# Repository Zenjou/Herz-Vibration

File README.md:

# Herz Vibration
Project for Electronic Equipment Design Course ( ELO301 Federico Santa María Technical University)

Group 6 
 - Victor Muñoz Salinas
 - Josefa Gomez
 - Diego Muñoz
 - Maximiliano Lara

# Description:
This project focuses on designing a PCB for real-time seismocardiograms utilizing geophones. Geophones efficiently capture vibrations produced by cardiac activity (Seismocardiography) . The custom-designed PCB seamlessly integrates with existing software, enabling efficient signal processing and in-depth analysis. Eagle PCB schematics, manufacturing files (including Gerber files and drill files), and a comprehensive Bill of Materials (BOM) are provided for straightforward replication.

# Features:
Custom-designed PCB optimized for seamless integration with geophones.

Eagle PCB schematics for a thorough understanding and easy modification.

Inclusion of all essential manufacturing files, including Gerber files and drill files, for PCB fabrication.

Utilizes the STM32 NUCLEO-L452 development board for enhanced functionality.

# Technologies Used:
Eagle PCB for schematic design.

Geophonic sensors for vibration capture (3 Geophones for each axis).

STM32 NUCLEO-L452 development board.

**SerialPlot by Hasan Yavuz Özderya for graphical visualization.**

ADS131M03 3-channel, 24-bit, 64 kSPS simultaneous sampling delta-sigma ADC.

# Files:
Eagle PCB Schematics

Manufacturing Files (Gerber, Drill Files, etc.)

BOM File

Videos

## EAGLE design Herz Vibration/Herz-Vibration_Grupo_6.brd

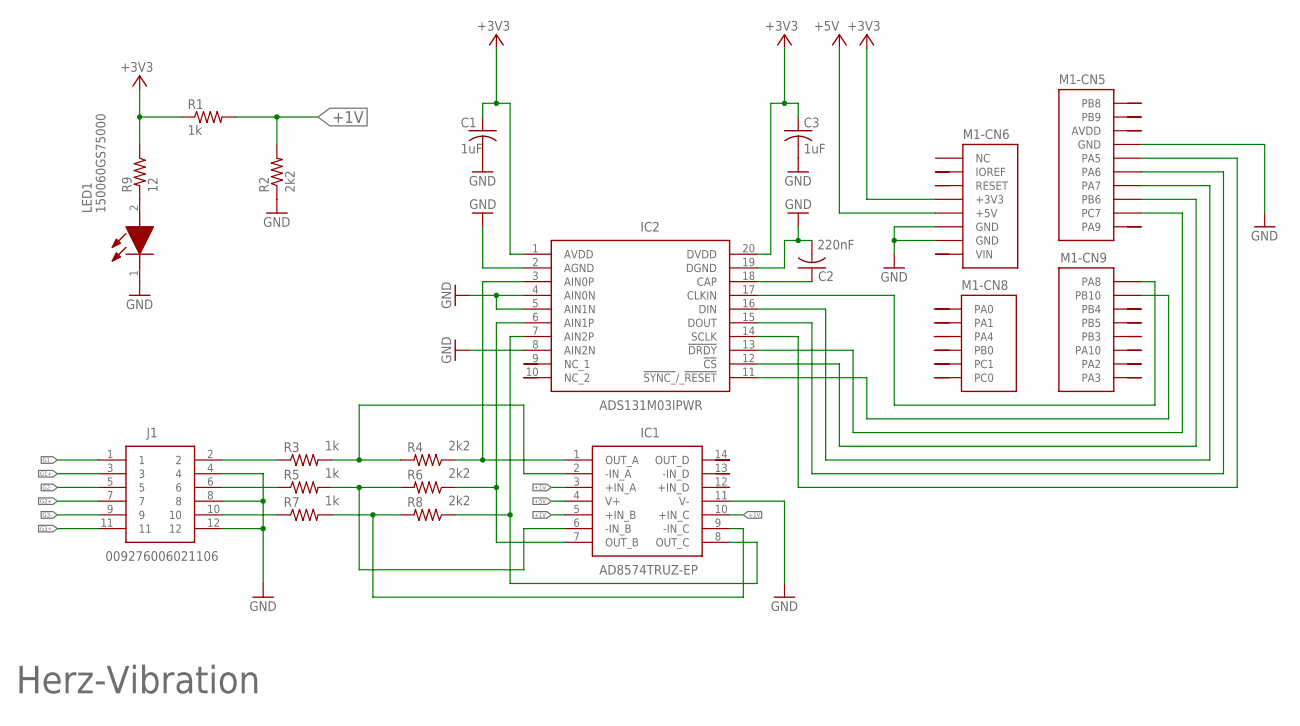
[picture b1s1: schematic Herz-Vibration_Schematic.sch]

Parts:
C1, C3: 1uF; C0805; PARTNO C1206C105K3RAC7215
C2: 220nF; C0805; PARTNO 885382207008
IC1: AD8574TRUZ-EP; SOP65P640X120-14N
IC2: ADS131M03IPWR; SOP65P640X120-20N
J1: 009276006021106
LED1: 150060GS75000; LEDC1608X80N
M1: NUCLEO-L452RE; NUCLEO-64
R1, R3, R5, R7: 1k; R0805; PARTNO TNPW04021K15BYEP
R2, R4, R6, R8: 2k2; R0805; PARTNO RP0603BRD072K2L
R9: 12; R0805; PARTNO RT0603DRE0712RL

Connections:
+1V: IC1.3 (+IN_A), IC1.5 (+IN_B), IC1.10 (+IN_C), R1.2, R2.2
+3V3: C1.1, C3.1, IC2.1 (AVDD), IC2.20 (DVDD), M1.CN6-4 (+3V3), M1.CN7-16 (+3V3), R1.1, R9.1
+5V: IC1.4 (V+), M1.CN6-5 (+5V), M1.CN7-18 (+5V)
AGND: M1.CN10-32 (AGND)
AVDD: M1.CN10-7 (AVDD)
G1+: J1.3
G1-: J1.1
G2+: J1.7
G2-: J1.5
G3+: J1.11
G3-: J1.9
GND: C1.2, C2.2, C3.2, IC1.11 (V-), IC2.2 (AGND), IC2.4 (AIN0N), IC2.5 (AIN1N), IC2.8 (AIN2N), IC2.19 (DGND), J1.4, J1.8, J1.12, LED1.1 (K), M1.CN5-7 (GND), M1.CN6-6 (GND), M1.CN6-7 (GND), M1.CN7-8 (GND), M1.CN7-19 (GND), M1.CN7-20 (GND), M1.CN7-22 (GND), M1.CN10-9 (GND), M1.CN10-20 (GND), R2.1
unnamed: IC1.1 (OUT_A), IC2.3 (AIN0P), R4.1
unnamed: IC1.7 (OUT_B), IC2.6 (AIN1P), R6.1
unnamed: IC1.8 (OUT_C), IC2.7 (AIN2P), R8.1
unnamed: IC1.2 (-IN_A), R3.2, R4.2
unnamed: IC1.9 (-IN_C), R7.2, R8.2
unnamed: IC1.6 (-IN_B), R5.2, R6.2
unnamed: J1.2, R3.1
unnamed: IC2.14 (SCLK), M1.CN5-6 (PA5)
unnamed: J1.6, R5.1
unnamed: J1.10, R7.1
unnamed: IC2.13 (!DRDY), M1.CN5-2 (PC7)
unnamed: IC2.12 (!CS), M1.CN5-3 (PB6)
unnamed: LED1.2 (A), R9.2
unnamed: C2.1, IC2.18 (CAP)
unnamed: IC2.17 (CLKIN), M1.CN9-8 (PA8)
unnamed: IC2.11 (!SYNC_!/_!RESET), M1.CN9-7 (PB10)
unnamed: IC2.16 (DIN), M1.CN5-4 (PA7)
unnamed: IC2.15 (DOUT), M1.CN5-5 (PA6)
U5V: M1.CN10-8 (U5V)
VBAT: M1.CN7-33 (VBAT)
VDD: M1.CN7-5 (VDD)
VIN: M1.CN7-24 (VIN)

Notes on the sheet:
Herz-Vibration

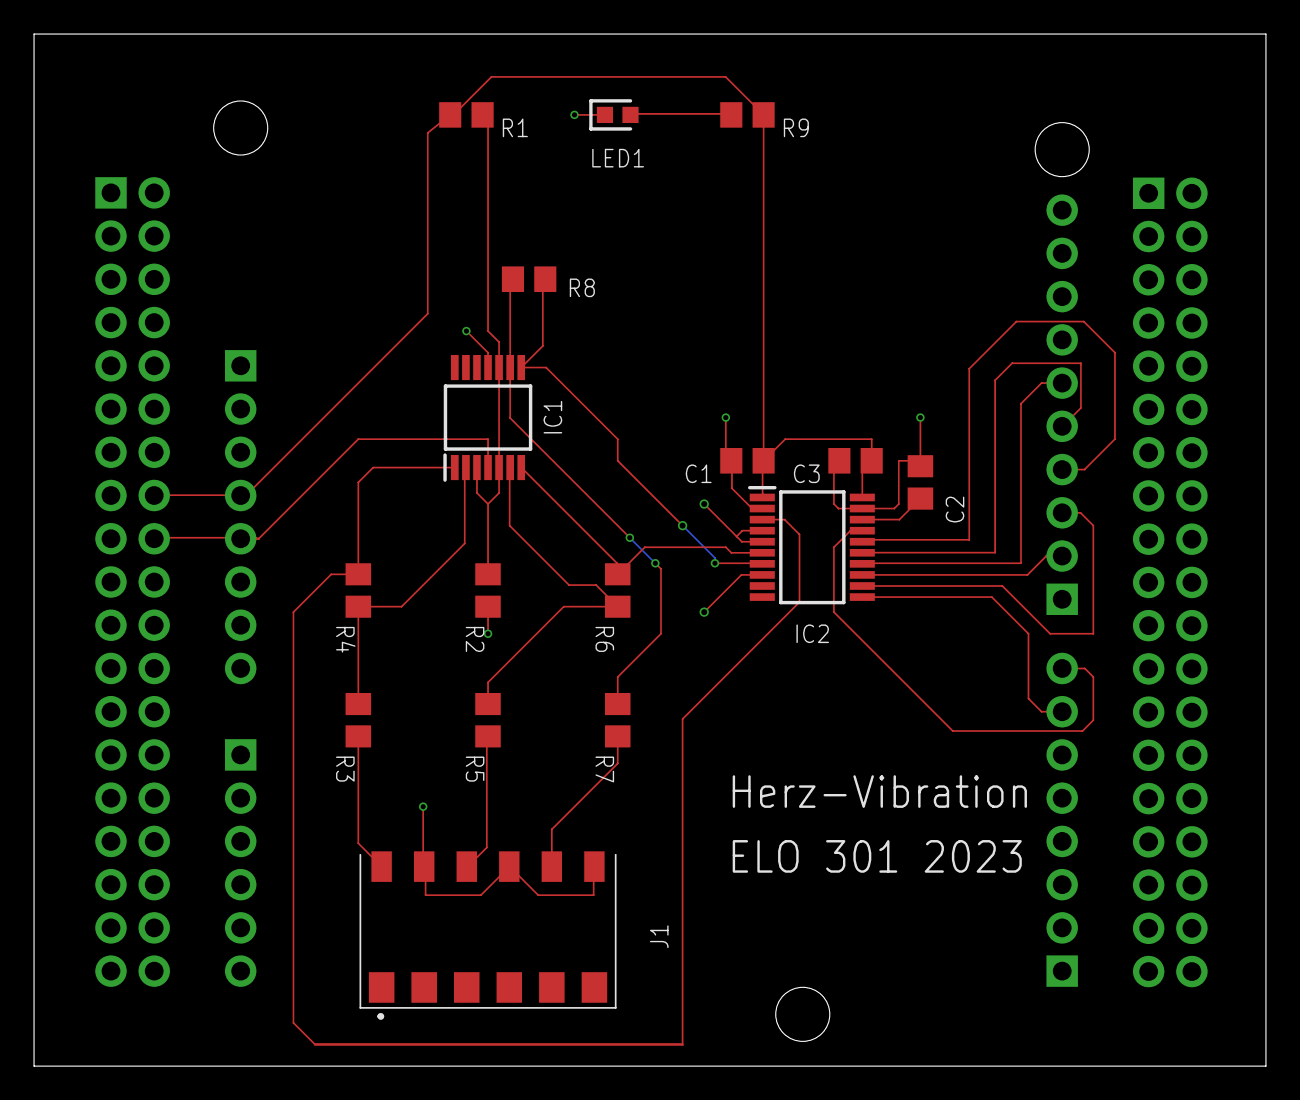
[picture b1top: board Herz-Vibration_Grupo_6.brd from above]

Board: 2 copper layers, 72.4 x 60.6 mm, 17 parts (0 on the bottom side), 22 nets.

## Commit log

2023-10-19 Project and Schematic Folder.
2023-10-19 Rename Esquematico_Grupo_6.sch to Esquematico_Grupo_6_V2.sch
2023-11-10 Actualización de esquemáticos y PCB.
2023-11-10 Rename Herz-Vibration_Grupo_6.csv to Herz-Vibration_Grupo_6_BOM.csv
    BOM
2023-11-10 Rename Herz-Vibration_Grupo_6_BOM.csv to Herz-Vibration_BOM.csv
2023-11-10 Rename Herz-Vibration_Grupo_6.brd to Herz-Vibration_PCB.brd
2023-11-10 Rename Herz-Vibration_Grupo_6.sch to Herz-Vibration_schematic.sch
2024-01-19 Rename Herz-Vibration_Grupo_6_2023-11-10.zip to Herz-Vibration_Manufacturing_Files.zip
2024-01-19 Rename Herz-Vibration_schematic.sch to Herz-Vibration_Schematic.sch
